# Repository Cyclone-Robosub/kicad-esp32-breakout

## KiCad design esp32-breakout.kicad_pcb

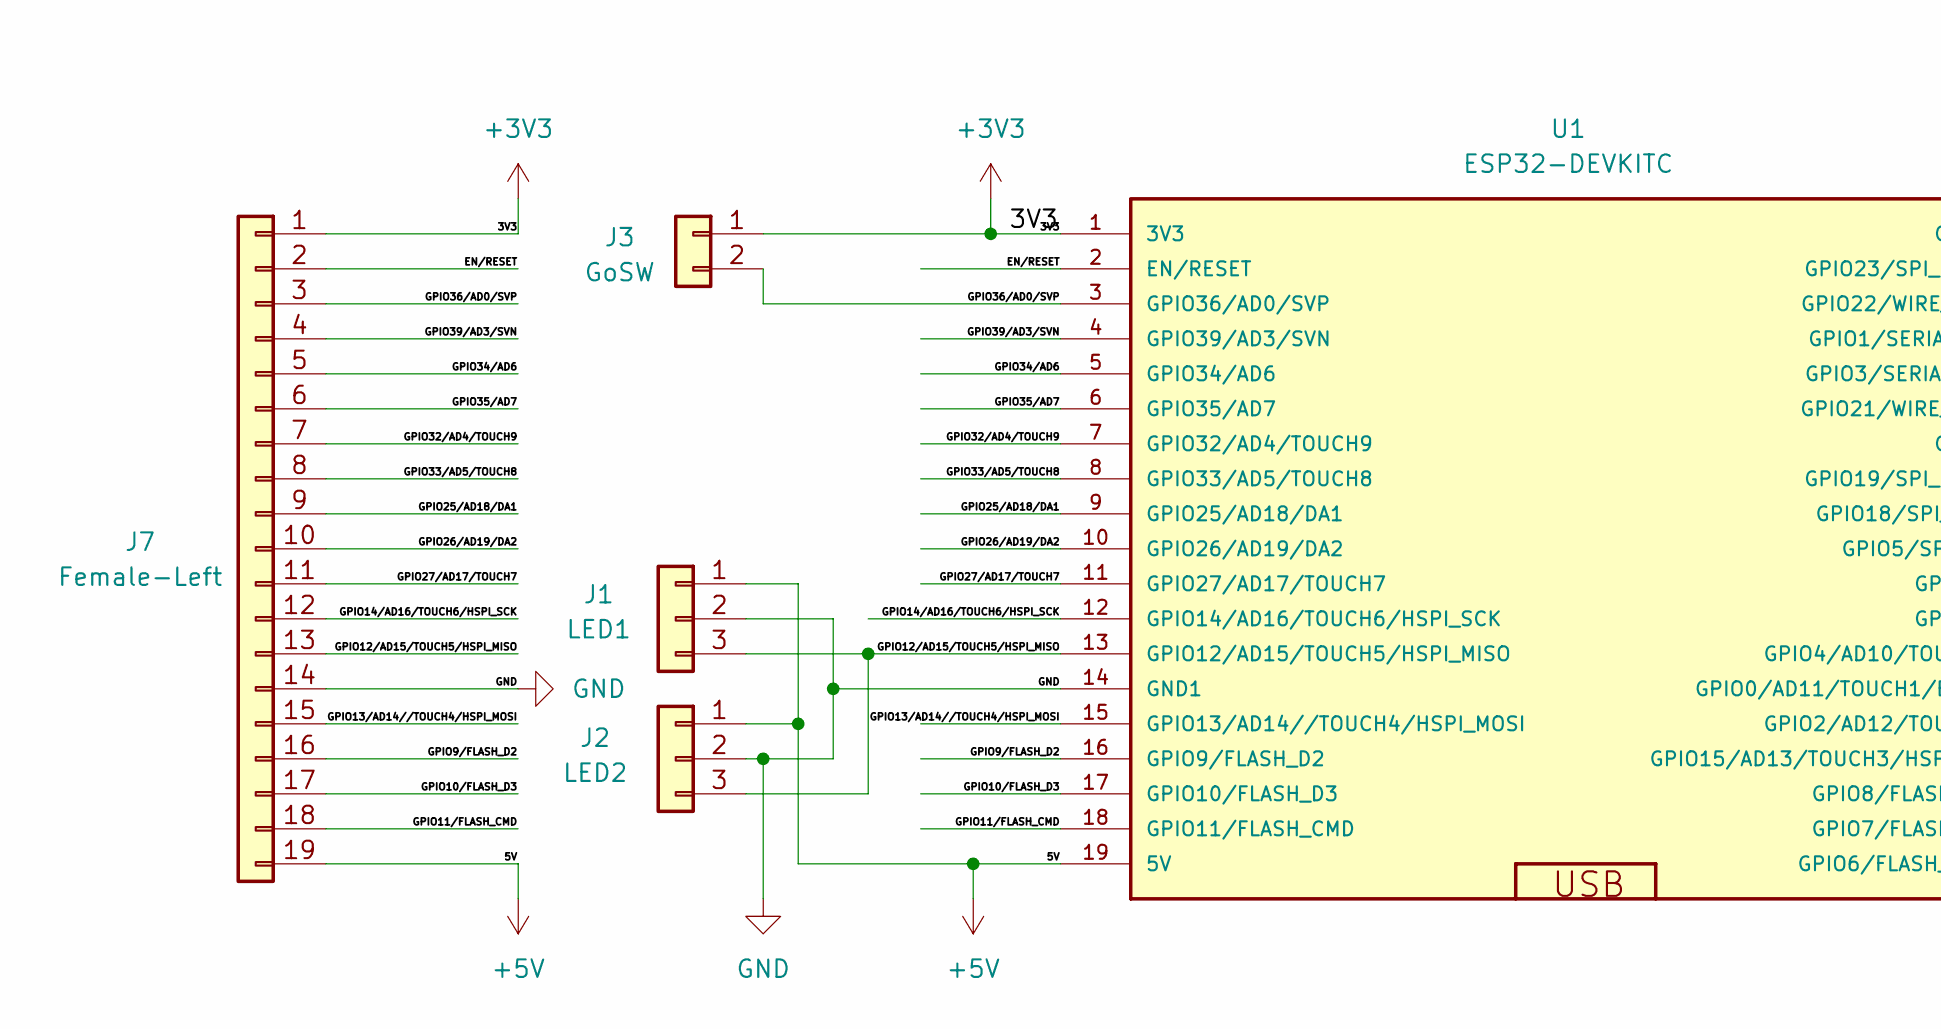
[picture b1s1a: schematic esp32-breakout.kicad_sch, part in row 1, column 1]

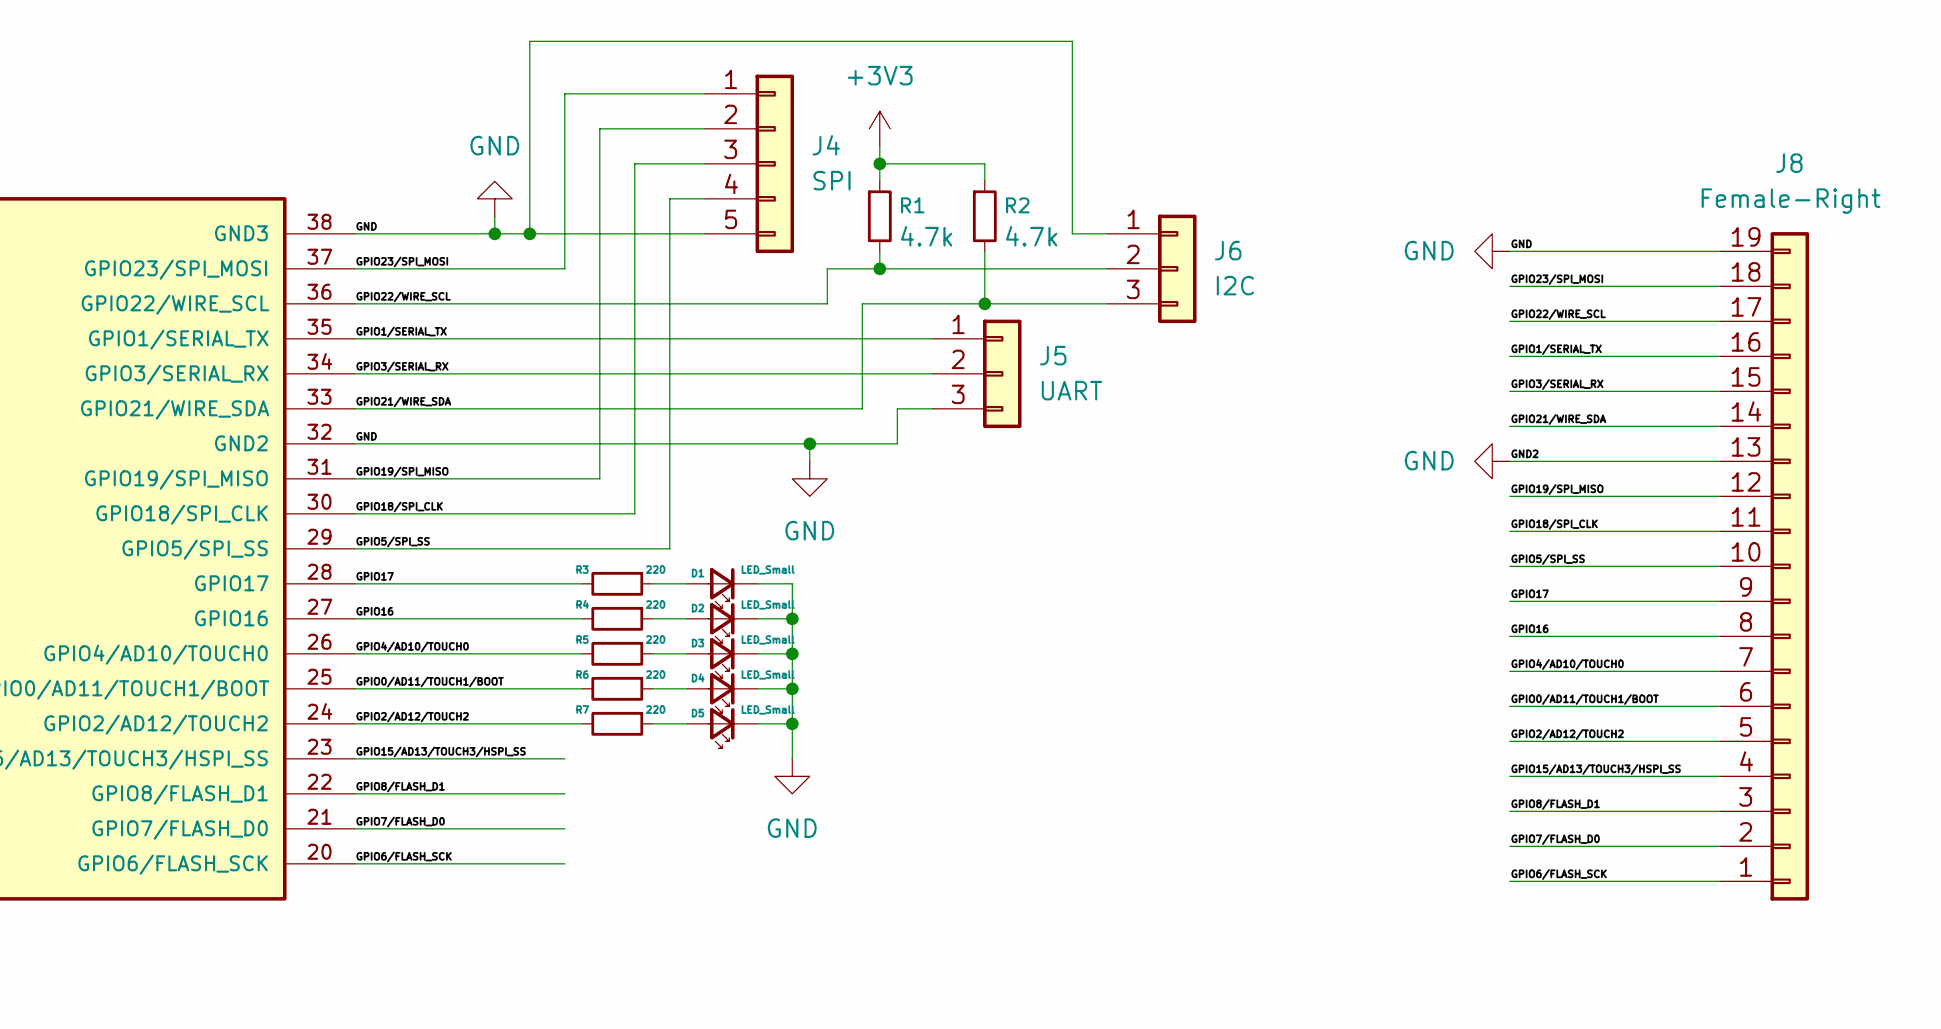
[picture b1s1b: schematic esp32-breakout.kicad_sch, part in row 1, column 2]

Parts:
D1, D2, D3, D4, D5: LED_Small; LED_0805_2012Metric_Pad1.15x1.40mm_HandSolder
J1: LED1; JST_PH_B3B-PH-K_1x03_P2.00mm_Vertical
J2: LED2; JST_PH_B3B-PH-K_1x03_P2.00mm_Vertical
J3: GoSW; JST_PH_B2B-PH-K_1x02_P2.00mm_Vertical
J4: SPI; JST_PH_B5B-PH-K_1x05_P2.00mm_Vertical
J5: UART; JST_PH_B3B-PH-K_1x03_P2.00mm_Vertical
J6: I2C; JST_PH_B3B-PH-K_1x03_P2.00mm_Vertical
J7: Female-Left; PinSocket_1x19_P2.54mm_Vertical
J8: Female-Right; PinSocket_1x19_P2.54mm_Vertical
R1, R2: 4.7k; R_0805_2012Metric_Pad1.20x1.40mm_HandSolder
R3, R4, R5, R6, R7: 220; R_0805_2012Metric_Pad1.20x1.40mm_HandSolder
U1: ESP32-DEVKITC

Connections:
+3V3: J3.1, J7.1, R1.1, R2.1, U1.1 (3V3)
+5V: J1.1, J2.1, J7.19, U1.19 (5V)
/EN/RESET: J7.2, U1.2 (EN/RESET)
/GPIO0/AD11/TOUCH1/BOOT: J8.6, R6.2, U1.25 (GPIO0/AD11/TOUCH1/BOOT)
/GPIO1/SERIAL_TX: J5.1, J8.16, U1.35 (GPIO1/SERIAL_TX)
/GPIO2/AD12/TOUCH2: J8.5, R7.2, U1.24 (GPIO2/AD12/TOUCH2)
/GPIO3/SERIAL_RX: J5.2, J8.15, U1.34 (GPIO3/SERIAL_RX)
/GPIO4/AD10/TOUCH0: J8.7, R5.2, U1.26 (GPIO4/AD10/TOUCH0)
/GPIO5/SPI_SS: J4.4, J8.10, U1.29 (GPIO5/SPI_SS)
/GPIO6/FLASH_SCK: J8.1, U1.20 (GPIO6/FLASH_SCK)
/GPIO7/FLASH_D0: J8.2, U1.21 (GPIO7/FLASH_D0)
/GPIO8/FLASH_D1: J8.3, U1.22 (GPIO8/FLASH_D1)
/GPIO9/FLASH_D2: J7.16, U1.16 (GPIO9/FLASH_D2)
/GPIO10/FLASH_D3: J7.17, U1.17 (GPIO10/FLASH_D3)
/GPIO11/FLASH_CMD: J7.18, U1.18 (GPIO11/FLASH_CMD)
/GPIO12/AD15/TOUCH5/HSPI_MISO: J1.3, J2.3, J7.13, U1.13 (GPIO12/AD15/TOUCH5/HSPI_MISO)
/GPIO13/AD14//TOUCH4/HSPI_MOSI: J7.15, U1.15 (GPIO13/AD14//TOUCH4/HSPI_MOSI)
/GPIO14/AD16/TOUCH6/HSPI_SCK: J7.12, U1.12 (GPIO14/AD16/TOUCH6/HSPI_SCK)
/GPIO15/AD13/TOUCH3/HSPI_SS: J8.4, U1.23 (GPIO15/AD13/TOUCH3/HSPI_SS)
/GPIO16: J8.8, R4.2, U1.27 (GPIO16)
/GPIO17: J8.9, R3.2, U1.28 (GPIO17)
/GPIO18/SPI_CLK: J4.3, J8.11, U1.30 (GPIO18/SPI_CLK)
/GPIO19/SPI_MISO: J4.2, J8.12, U1.31 (GPIO19/SPI_MISO)
/GPIO21/WIRE_SDA: J6.3, J8.14, R2.2, U1.33 (GPIO21/WIRE_SDA)
/GPIO22/WIRE_SCL: J6.2, J8.17, R1.2, U1.36 (GPIO22/WIRE_SCL)
/GPIO23/SPI_MOSI: J4.1, J8.18, U1.37 (GPIO23/SPI_MOSI)
/GPIO25/AD18/DA1: J7.9, U1.9 (GPIO25/AD18/DA1)
/GPIO26/AD19/DA2: J7.10, U1.10 (GPIO26/AD19/DA2)
/GPIO27/AD17/TOUCH7: J7.11, U1.11 (GPIO27/AD17/TOUCH7)
/GPIO32/AD4/TOUCH9: J7.7, U1.7 (GPIO32/AD4/TOUCH9)
/GPIO33/AD5/TOUCH8: J7.8, U1.8 (GPIO33/AD5/TOUCH8)
/GPIO34/AD6: J7.5, U1.5 (GPIO34/AD6)
/GPIO35/AD7: J7.6, U1.6 (GPIO35/AD7)
/GPIO36/AD0/SVP: J3.2, J7.3, U1.3 (GPIO36/AD0/SVP)
/GPIO39/AD3/SVN: J7.4, U1.4 (GPIO39/AD3/SVN)
GND: D1.1 (K), D2.1 (K), D3.1 (K), D4.1 (K), D5.1 (K), J1.2, J2.2, J4.5, J5.3, J6.1, J7.14, J8.13, J8.19, U1.14 (GND1), U1.32 (GND2), U1.38 (GND3)
unnamed: D1.2 (A), R3.1
unnamed: D2.2 (A), R4.1
unnamed: D3.2 (A), R5.1
unnamed: D4.2 (A), R6.1
unnamed: D5.2 (A), R7.1

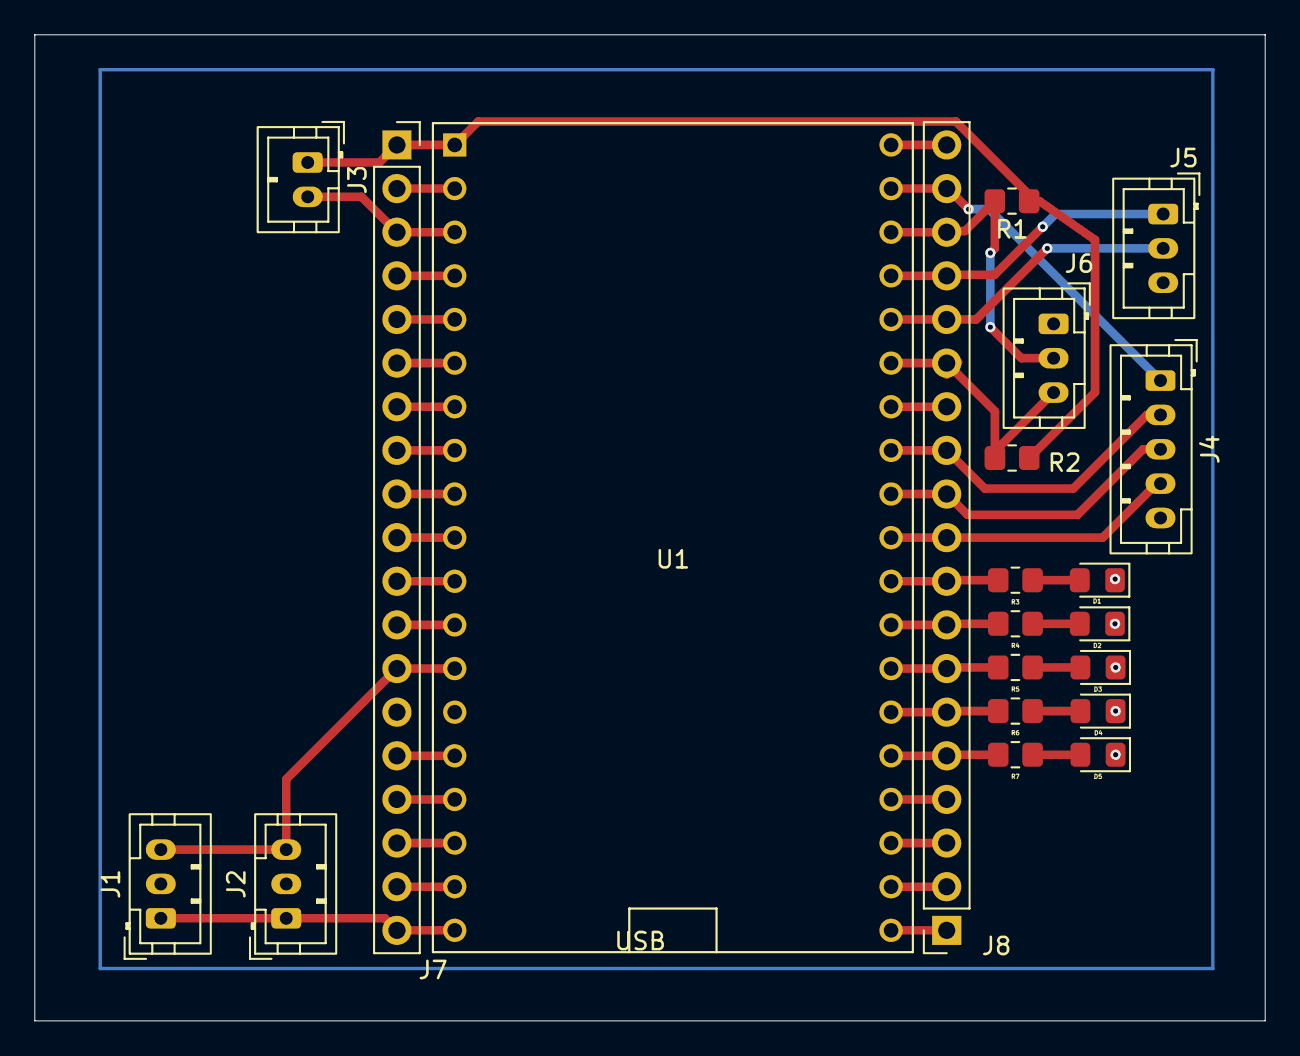
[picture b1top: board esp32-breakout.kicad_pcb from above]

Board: 2 copper layers, 71.6 x 57.4 mm, 21 parts (0 on the bottom side), 41 nets.
